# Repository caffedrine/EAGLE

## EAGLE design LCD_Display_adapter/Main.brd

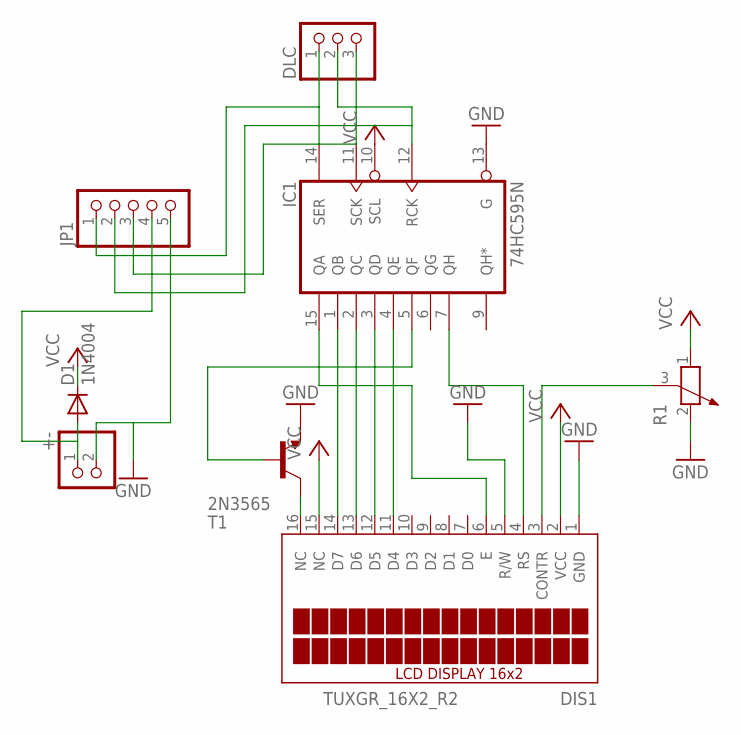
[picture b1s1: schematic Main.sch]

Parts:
+-: PINHD-1X2; 1X02
D1: 1N4004; DO41-10
DIS1: TUXGR_16X2_R2
DLC: PINHD-1X3; 1X03
IC1: 74HC595N; DIL16
JP1: PINHD-1X5/90; 1X05/90
R1: POTENTIOMETER_PT-10; PT-10
T1: 2N3565; TO92

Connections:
GND: +-.2, DIS1.1 (GND), DIS1.5 (R/W), IC1.8 (GND), IC1.13 (G), JP1.5, R1.2, T1.3 (E)
unnamed: DIS1.14 (D7), IC1.1 (QB)
unnamed: DIS1.13 (D6), IC1.2 (QC)
unnamed: DIS1.12 (D5), IC1.3 (QD)
unnamed: DIS1.11 (D4), IC1.4 (QE)
unnamed: +-.1, D1.A, JP1.4
unnamed: DIS1.16 (NC), T1.1 (C)
unnamed: DIS1.6 (E), IC1.15 (QA)
unnamed: DIS1.3 (CONTR), R1.3
unnamed: DIS1.4 (RS), IC1.7 (QH)
unnamed: DLC.3, IC1.11 (SCK), JP1.3
unnamed: IC1.5 (QF), T1.2 (B)
unnamed: DLC.1, IC1.14 (SER), JP1.1
unnamed: DLC.2, IC1.12 (RCK), JP1.2
VCC: D1.C, DIS1.2 (VCC), DIS1.15 (NC), IC1.10 (SCL), IC1.16 (VCC), R1.1

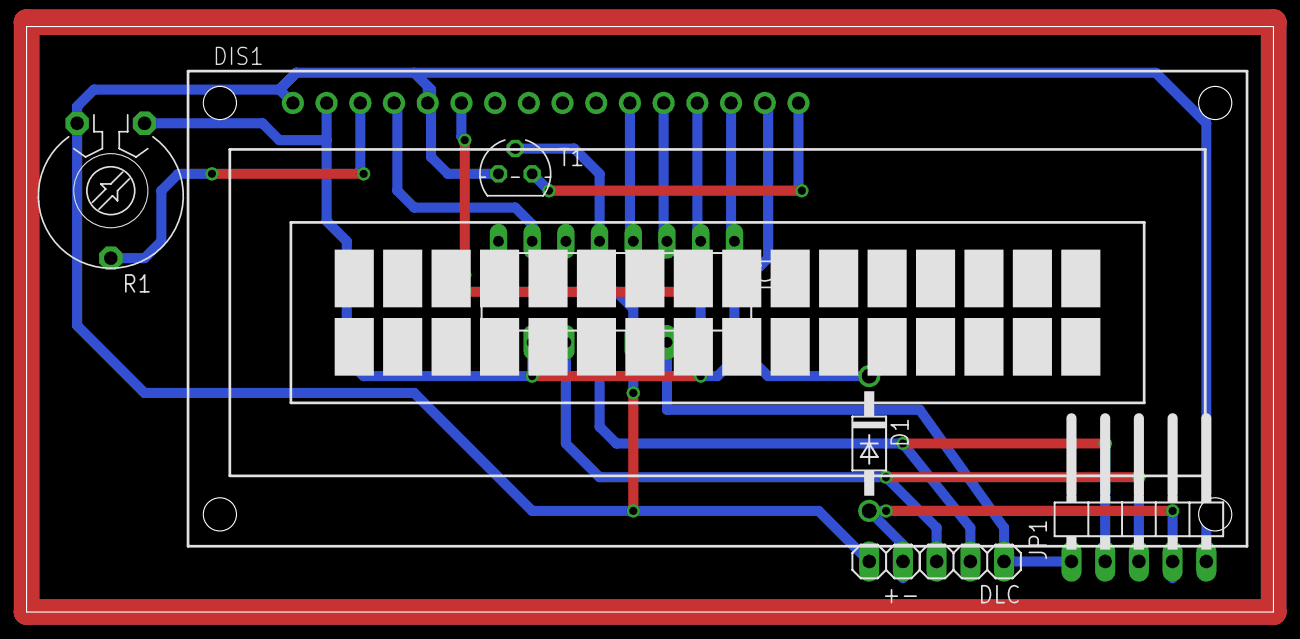
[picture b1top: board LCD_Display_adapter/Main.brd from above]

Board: 2 copper layers, 94.0 x 44.1 mm, 8 parts (0 on the bottom side), 15 nets.

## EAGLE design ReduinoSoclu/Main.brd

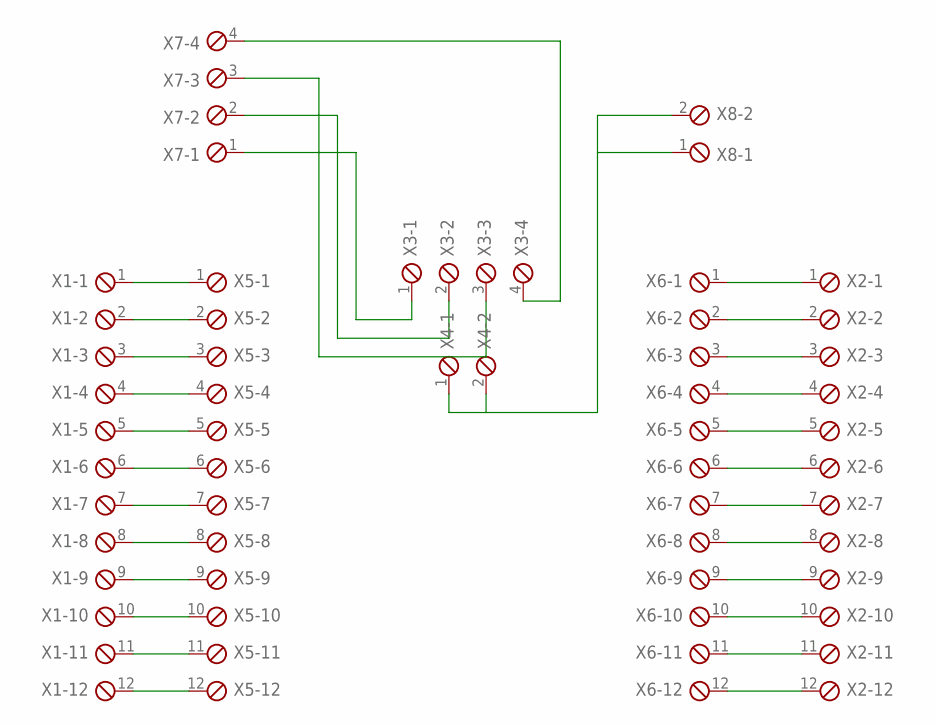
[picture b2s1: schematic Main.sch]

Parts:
X1, X2, X5, X6: MPT12; 12POL254
X3, X7: MPT4; 4POL254
X4, X8: MPT2; 2POL254

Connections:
unnamed: X1.1, X5.1
unnamed: X1.2, X5.2
unnamed: X1.3, X5.3
unnamed: X1.4, X5.4
unnamed: X1.5, X5.5
unnamed: X1.6, X5.6
unnamed: X1.7, X5.7
unnamed: X1.8, X5.8
unnamed: X1.9, X5.9
unnamed: X1.10, X5.10
unnamed: X1.11, X5.11
unnamed: X1.12, X5.12
unnamed: X2.1, X6.1
unnamed: X2.2, X6.2
unnamed: X2.3, X6.3
unnamed: X2.4, X6.4
unnamed: X2.5, X6.5
unnamed: X2.6, X6.6
unnamed: X2.7, X6.7
unnamed: X2.8, X6.8
unnamed: X2.9, X6.9
unnamed: X2.10, X6.10
unnamed: X2.11, X6.11
unnamed: X2.12, X6.12
unnamed: X3.1, X7.1
unnamed: X3.2, X7.2
unnamed: X3.3, X7.3
unnamed: X3.4, X7.4
unnamed: X4.1, X4.2, X8.1, X8.2

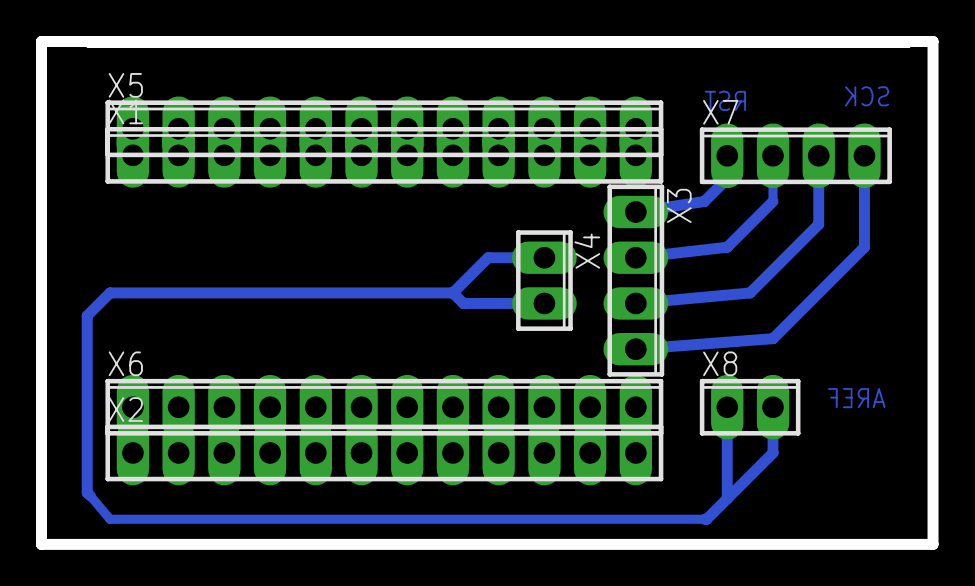
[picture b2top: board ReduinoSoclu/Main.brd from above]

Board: 2 copper layers, 49.5 x 27.9 mm, 8 parts (0 on the bottom side), 29 nets.

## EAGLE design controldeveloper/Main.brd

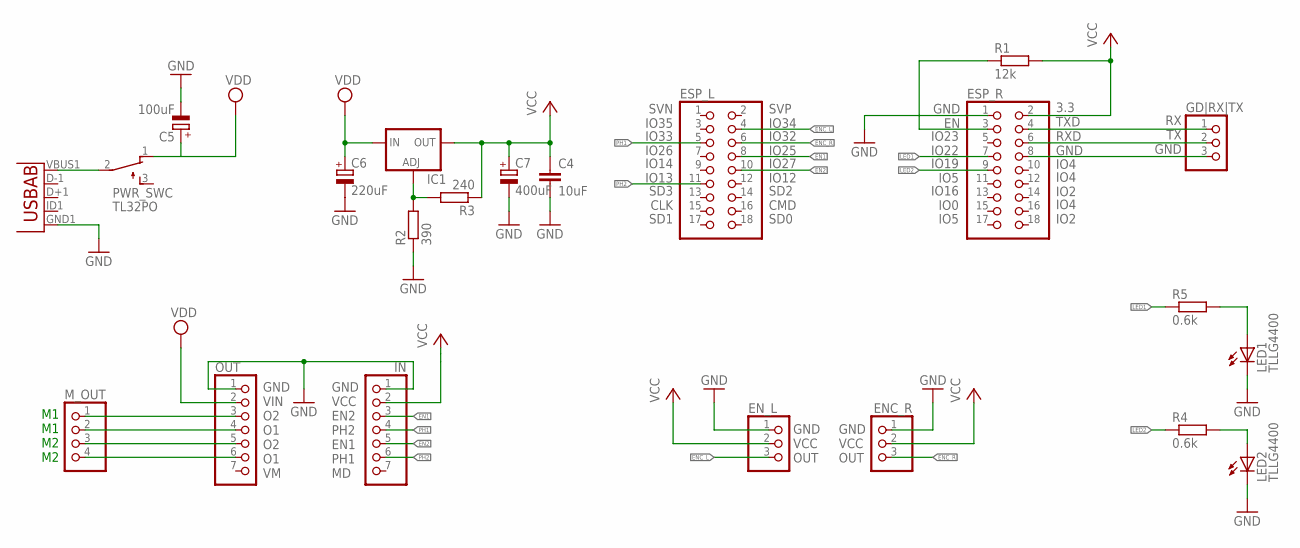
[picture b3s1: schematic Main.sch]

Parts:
C4: 10uF; C050-025X075
C5: 100uF; E2,5-6
C6: 220uF; E2,5-6
C7: 400uF; E2,5-6
ENC_R: PINHD-1X3; 1X03
EN_L: PINHD-1X3; 1X03
ESP_L: PINHD-2X9; 2X09
ESP_R: PINHD-2X9; 2X09
GD|RX|TX: PINHD-1X3; 1X03
IC1: LM317TS; 317TS
IN: PINHD-1X7; 1X07
LED1, LED2: TLLG4400; LED3MM
M_OUT: PINHD-1X4; 1X04
OUT: PINHD-1X7; 1X07
PWR_SWC: TL32PO; TL3XPO
R1: 12k; 0207/10
R2: 390; 0207/10
R3: 240; 0207/10
R4, R5: 0.6k; 0207/10
U3: USB""; USB-MICRO-SMD

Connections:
EN1: ESP_L.8, IN.3
EN2: ESP_L.10, IN.5
ENC_L: EN_L.3, ESP_L.4
ENC_R: ENC_R.3, ESP_L.6
GND: C4.2, C5.-, C6.-, C7.-, ENC_R.1, EN_L.1, ESP_R.1, IN.1, LED1.K (C), LED2.K (C), OUT.1, R2.1, U3.GND1 (GND)
LED1: ESP_R.7, R5.1
LED2: ESP_R.9, R4.1
unnamed: M_OUT.1, OUT.3
unnamed: M_OUT.2, OUT.4
unnamed: M_OUT.3, OUT.5
unnamed: M_OUT.4, OUT.6
unnamed: ESP_R.4, GD|RX|TX.1
unnamed: ESP_R.6, GD|RX|TX.2
unnamed: IC1.1 (ADJ), R2.2, R3.2
unnamed: ESP_R.8, GD|RX|TX.3
unnamed: LED2.A, R4.2
unnamed: PWR_SWC.2, U3.VBUS1 (VBUS)
unnamed: ESP_R.3, R1.1
unnamed: LED1.A, R5.2
PH1: ESP_L.5, IN.4
PH2: ESP_L.11, IN.6
VCC: C4.1, C7.+, ENC_R.2, EN_L.2, ESP_R.2, IC1.2 (OUT), IN.2, R1.2, R3.1
VDD: C5.+, C6.+, IC1.3 (IN), OUT.2, PWR_SWC.1 (O)

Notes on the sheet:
GND VCC EN2 PH2 EN1 PH1 MD
GND VIN O2 O1 O2 O1 VM
M1 M1 M2 M2
RX TX GND
GND VCC OUT
3.3 TXD RXD GND
IO4 IO2
GND EN
IO23 IO22
IO19 IO5
IO16 IO0
IO5
IO4
SVN IO35
IO33 IO26
IO14 IO13
SD3 CLK
SD1
SVP IO34
IO32 IO25
IO27 IO12
SD2 CMD
SD0

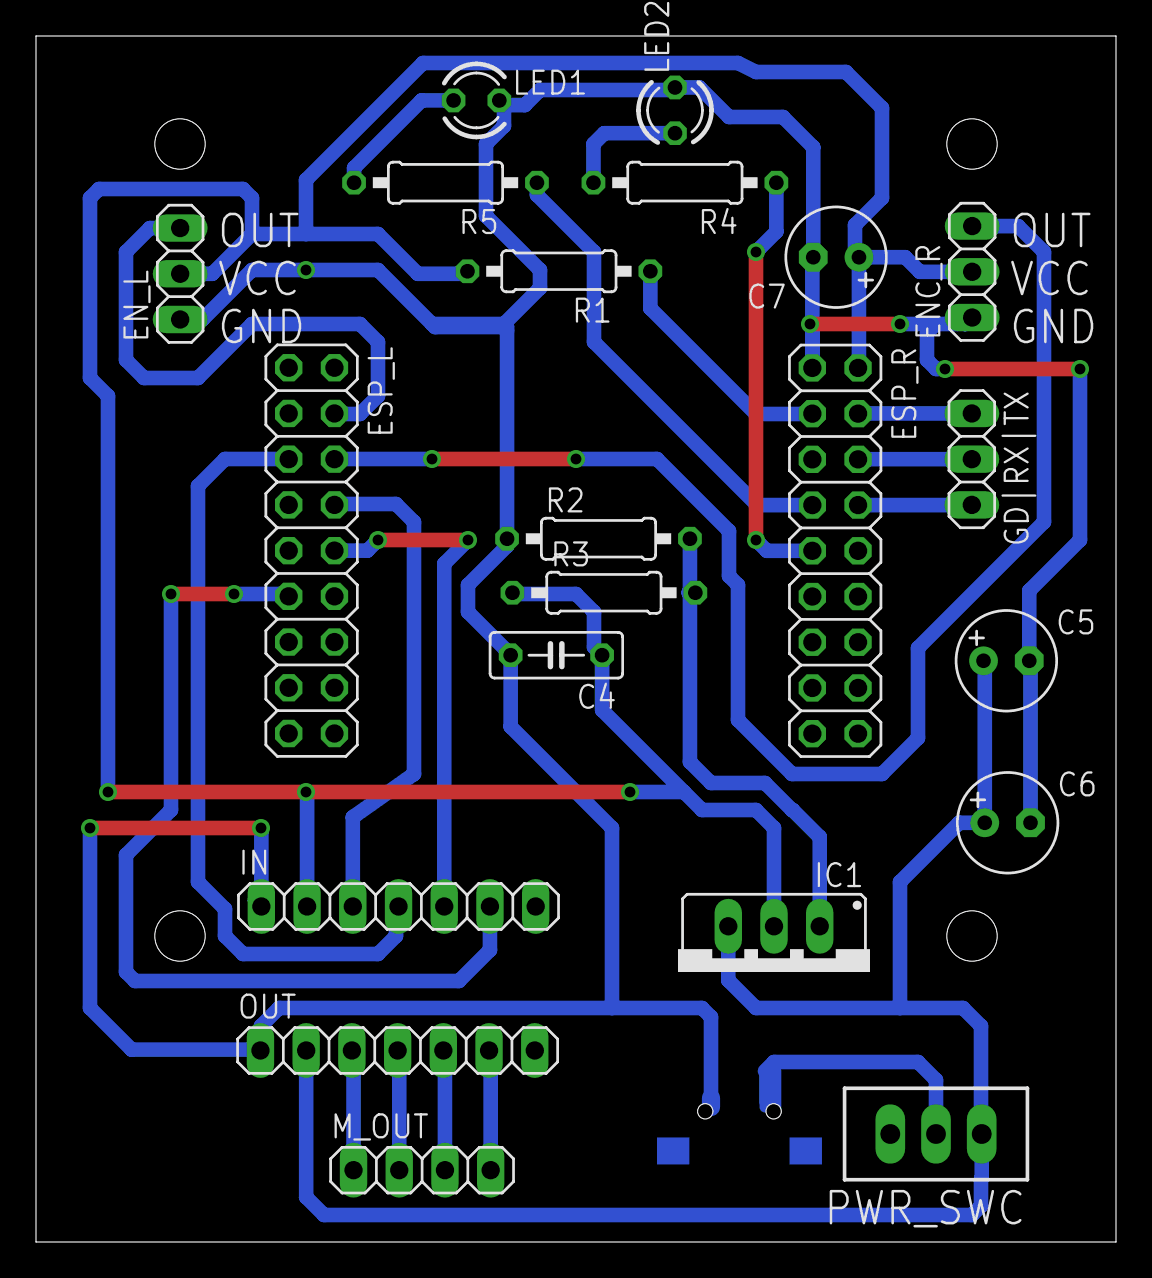
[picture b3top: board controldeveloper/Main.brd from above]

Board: 2 copper layers, 60.0 x 67.0 mm, 22 parts (1 on the bottom side), 23 nets.
